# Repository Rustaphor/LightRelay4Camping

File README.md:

LightRelay4Camping ⛺🌳⛰️
==========================

Проект аналогового микромощного фотореле с питанием от PowerBank (USB Type-C) для управления включение-отключение USB-гирлянд
(напряжения питания 5В) в ночное время суток в широким диапазоне регулировки пороговых уровней чувствительности к темноте.
Это простое и надежное DIY устройство целиком аналоговое без прошивок, его несложно повторить начинающему радиолюбителю.
На фото ниже представлен внешний вид собранной электронной платы и устройства в корпусе.

**Фото устройства в корпусе**

## Для чего нужно?
Устройство будет очень полезным в местах кемпинга и отдыха при освещении гирляндами с питанием от PowerBank-ов.
Светодиодные USB-гирлянды, украшающие палатку/автомобиль или другое место размещения на природе с помощью данного устройства
станут автономно-управляемые по уличной освещенности. Самостоятельно включаться в ночное время суток и также отключаться
на рассвете, тем самым экономя заряд PowerBank-а.

[][1]

## Особенности девайса
Фотореле спроектировано просто и надежно. Технически проект представляет несложную реализацию электронной аналоговой
схемотехники (см. _принципиальную схему_) и стандартной цифровой логики (без микроконтроллеров и прошивок), что делает прибор
микро мощным малопотребляемым. А также последнее обстоятельство делает удобным повторение DIY, например в учебной практике.
Для построения электронной схемы выбраны современные широкодоступные электронные компоненты. Ниже кратко представлены
основные достоинства устройства:

- :white_check_mark: Сверхнизкое энергопотребление, значение всего 1мА (в светлое время);
- :white_check_mark: Широкий диапазон регулирования чувствительности срабатывания. От крайне темного, едва видное глазу до рассвета,
когда уже гирлянды не нужны;
- :white_check_mark: Питание 5В от повербанка USB Type-C;
- :white_check_mark: Встроенный супперконденсатор и схема его заряда для решение проблемы самоотключения PowerBank-ов. В ждущем режиме фотореле питается от собственного суперконденсатора.
  Емкости суперконденсатора хватает на 4 часа автономной работы;
- :white_check_mark: Небольшая встроенная временная задержка включения/отключения для минимизации ложных срабатываний часто меняющейся
освещенности, например, под качающимися кронами деревьев;
- 🎁 В качестве бонуса к проектe приложены исходные файлы корпуса для 3D-печати. Корпус имеет следующие особенности:
  - ☔︎ Влагозащищенный
  - 👁 Поворотный глазок с датчиком освещенности (направляется в небо)
  - 🧲 Магнитное крепление 

**Фото устройства со снятой верхней крышкой**

> [!TIP]
> PowerBank-и имеют особенность работы. Они предназначены для питания сравнительно мощных нагрузок. Если ток
> потребления нагрузкой слишком мал (менее 50…100мА), то через небольшой промежуток времени PowerBank переходит в режим
> «сна» (выключается), нагрузка полностью обесточивается.

:blue_book: [Полная техническая документация][1] содержит подробное описание принципа работы, инструкции к изготовлению.

> [!IMPORTANT]
> Подключение устройства к PowerBank-у рекомендуется кабелем *USB: type-C + type-C*. При использовании кабеля *USB: Type-A + Type-C*, автоматическое включение
> PowerBank-а негарантировано (зависит от особенностей конкретного PowerBank-а).

<details>
<summary>:paperclip: Файлы проекта</summary>

## Файлы проекта
Проект состоит из нижеследующих файлов и папок:

**Проектные файлы электронной схемы и печатной платы** в формате [KiCad EDA](https://www.kicad.org/) v8.0, содержат
электронную схему, печатную плату (ПП), правила её трассировки, сопутствующие компоненты (посадочные места, 3D-модели).

```
📄 Camping-LightRelay.kicad_*
📄 lsensor-module.kicad_sch
📄 custom.kicad_sym
📄 fp-lib-table
📄 sym-lib-table
📂 [lib.pretty]
📂 [3dshapes]
```

**Файлы симуляции**
Файлы симуляция [SPICE](https://ru.wikipedia.org/wiki/SPICE_(%D1%81%D0%B8%D0%BC%D1%83%D0%BB%D1%8F%D1%82%D0%BE%D1%80_%D1%8D%D0%BB%D0%B5%D0%BA%D1%82%D1%80%D0%BE%D0%BD%D0%BD%D1%8B%D1%85_%D1%81%D1%85%D0%B5%D0%BC))
отдельных узлов содержатся в отдельной директории

```
📂 [Sims]
```
</details>

[1]: https://github.com/Rustaphor/LightRelay4Camping/wiki "Перейти в раздел Wiki"

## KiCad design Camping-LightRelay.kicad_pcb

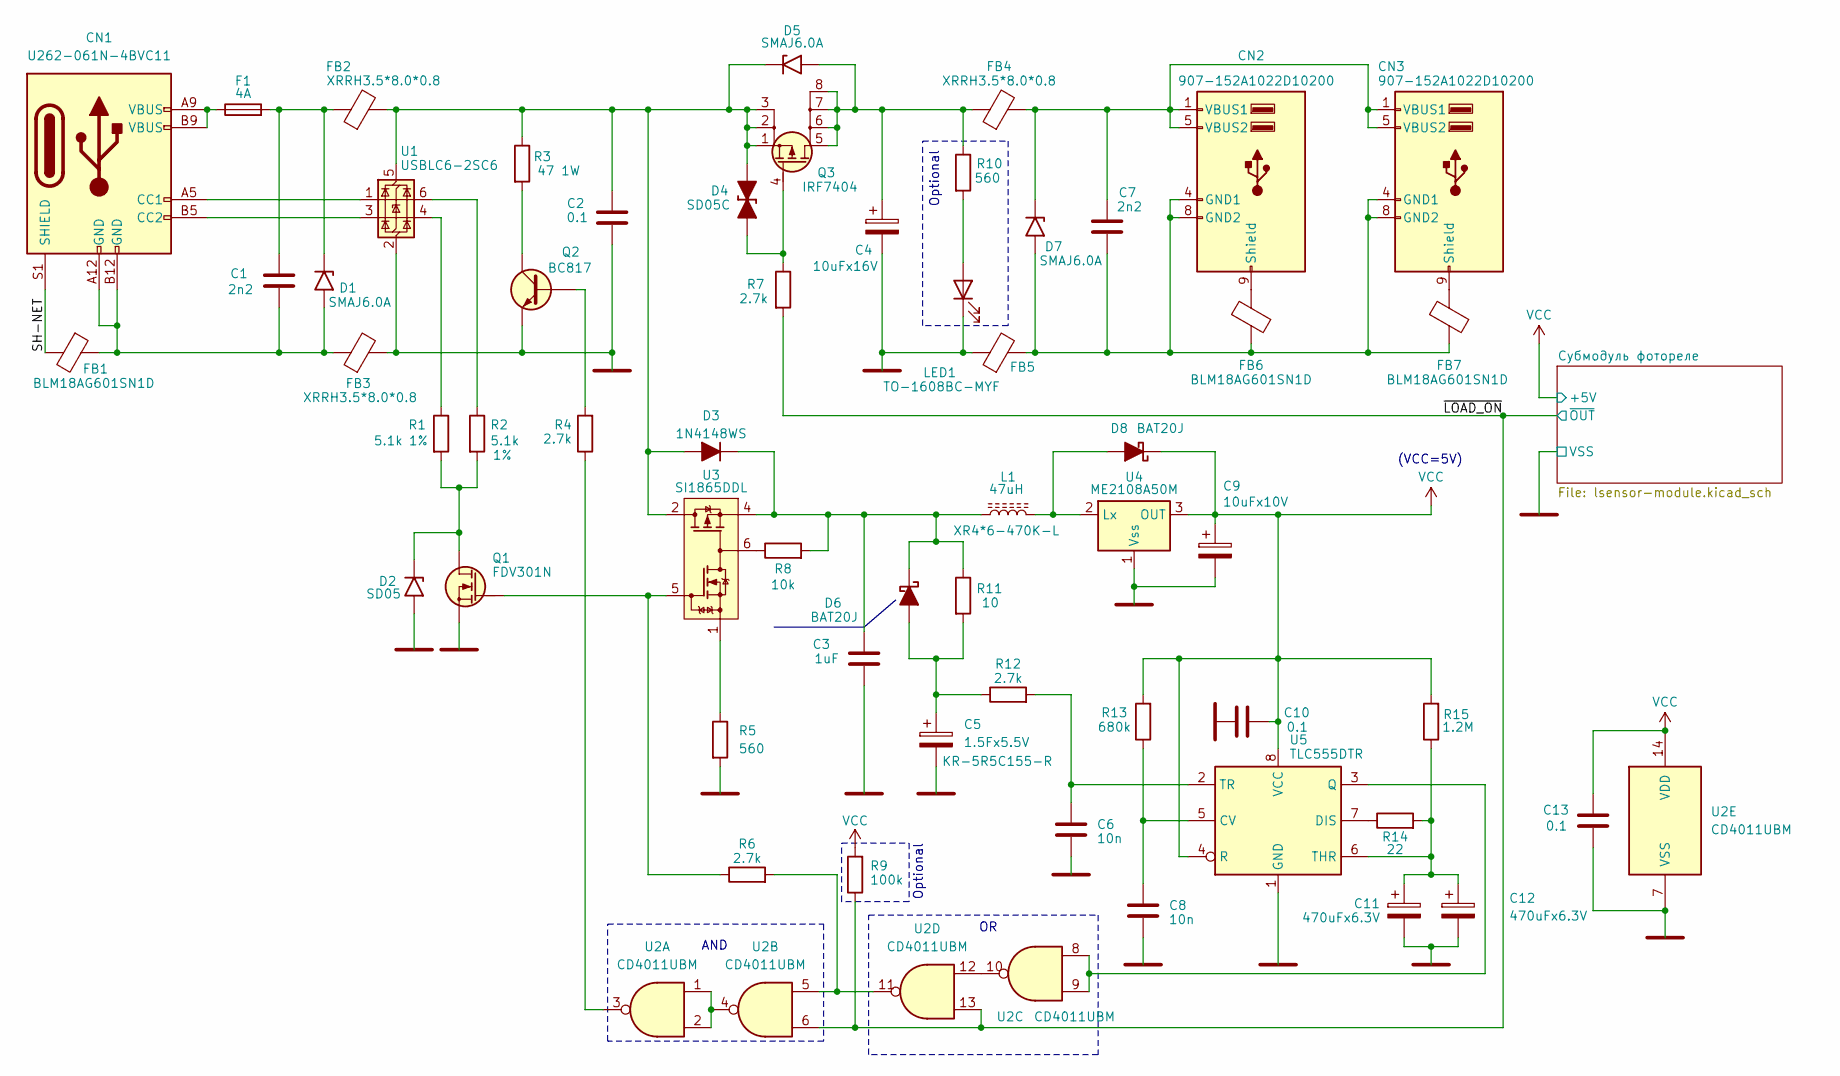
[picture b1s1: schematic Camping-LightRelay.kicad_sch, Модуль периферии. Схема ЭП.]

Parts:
C1, C7: 2n2; C_Disc_D7.5mm_W5.0mm_P7.50mm; Part Number CY2222MD1PEE47J2A8
C2, C10, C13: 0.1; C_0603_1608Metric
C3: 1uF; C_0805_2012Metric
C4: 10uFx16V; CP_EIA-3216-12_Kemet-S_Pad1.58x1.35mm_HandSolder; Part Number CA45-B010K107T
C5: 1.5Fx5.5V; Eaton_KR-5R5C155; Part Number KR-5R5C155-R
C6, C8: 10n; C_0603_1608Metric
C9: 10uFx10V; CP_EIA-3216-12_Kemet-S_Pad1.58x1.35mm_HandSolder; Part Number TC212A106K010Y
C11, C12: 470uFx6.3V; CP_EIA-7343-31_Kemet-D_Pad2.25x2.55mm_HandSolder; Part Number TAJD477K006RNJ
CN1: U262-061N-4BVC11; USB_C_Receptacle_GCT_USB4125-xx-x-0190_6P_TopMnt_Horizontal
CN2, CN3: 907-152A1022D10200; USB_A_DUAL_PORT_Horizontal_Stacked
D1, D5, D7: SMAJ6.0A; D_SMA
D2: SD05; D_SOD-323_HandSoldering
D3: 1N4148WS; D_SOD-323_HandSoldering
D4: SD05C; D_SOD-323_HandSoldering
D6, D8: BAT20J; D_SOD-323_HandSoldering
F1: 4A; Fuse_1206_3216Metric_Pad1.42x1.75mm_HandSolder
FB1, FB6, FB7: BLM18AG601SN1D; L_0603_1608Metric
FB2, FB3, FB4, FB5: XRRH3.5*8.0*0.8; Ferrite_L8.0mm_D3.5mm_P3.81mm_Vertical
L1: 47uH; L_Radial_D6.0mm_P4.00mm; Part Number XR4*6-470K-L
LED1: TO-1608BC-MYF; LED_0603_1608Metric_Pad1.05x0.95mm_HandSolder
Q1: FDV301N; SOT-23
Q2: BC817; SOT-23
Q3: IRF7404; SO-8_3.9x4.9mm_P1.27mm
R1, R2: 5.1k; R_0603_1608Metric_Pad0.98x0.95mm; Tolerance 1%
R3: 47 1W; R_Axial_DIN0309_L9.0mm_D3.2mm_P2.54mm_Vertical
R4, R6, R12: 2.7k; R_0603_1608Metric_Pad0.98x0.95mm
R5: 560; R_0603_1608Metric_Pad0.98x0.95mm
R7: 2.7k; R_0603_1608Metric
R8: 10k; R_0603_1608Metric_Pad0.98x0.95mm
R9: 100k; R_0603_1608Metric_Pad0.98x0.95mm
R10: 560; R_0603_1608Metric
R11: 10; R_0805_2012Metric_Pad1.15x1.40mm
R13: 680k; R_0603_1608Metric_Pad0.98x0.95mm
R14: 22; R_0603_1608Metric_Pad0.98x0.95mm
R15: 1.2M; R_0603_1608Metric_Pad0.98x0.95mm
U1: USBLC6-2SC6; SOT-23-6
U2: CD4011UBM; SOIC-14_3.9x8.7mm_P1.27mm
U3: SI1865DDL; SOT-363_SC-70-6
U4: ME2108A50M; SOT-23-3
U5: TLC555DTR; SOIC-8_3.9x4.9mm_P1.27mm

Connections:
/SH-NET: CN1.S1 (SHIELD), FB1.2
/~LOAD_ON: R7.2, R9.1, U2.6, U2.13; also elsewhere on the board
GNDE: C2.2, C3.2, C4.2, C5.2, C6.2, C8.2, C9.2, C10.1, C11.2, C12.2, C13.2, D2.2 (A2), FB3.2, FB5.1, LED1.1 (K), Q1.2 (S), Q2.2 (E), R5.2, U1.2 (GND), U2.7 (VSS), U4.1 (Vss), U5.1 (GND); also elsewhere on the board
unnamed: CN1.A5 (CC1), U1.1 (I/O1)
unnamed: CN1.B5 (CC2), U1.3 (I/O2)
unnamed: CN1.A9 (VBUS), CN1.B9 (VBUS), F1.1
unnamed: C7.2, CN2.4 (GND1), CN2.8 (GND2), CN3.4 (GND1), CN3.8 (GND2), D7.2 (A2), FB5.2, FB6.1, FB7.1
unnamed: CN2.9 (Shield), FB6.2
unnamed: C7.1, CN2.1 (VBUS1), CN2.5 (VBUS2), CN3.1 (VBUS1), CN3.5 (VBUS2), D7.1 (A1), FB4.2
unnamed: CN3.9 (Shield), FB7.2
unnamed: C1.1, D1.1 (A1), F1.2, FB2.1
unnamed: C1.2, CN1.A12 (GND), CN1.B12 (GND), D1.2 (A2), FB1.1, FB3.1
unnamed: D2.1 (A1), Q1.3 (D), R1.2, R2.2
unnamed: C2.1, D3.2 (A), D4.1 (K), D5.1 (A1), FB2.2, Q3.1 (S), Q3.2 (S), Q3.3 (S), R3.1, U1.5 (VBUS), U3.2 (D2), U3.3 (D2)
unnamed: C3.1, D3.1 (K), D6.1 (K), L1.1, R8.2, R11.1, U3.4 (S2)
unnamed: D4.2 (A), Q3.4 (G), R7.1
unnamed: C4.1, D5.2 (A2), FB4.1, Q3.5 (D), Q3.6 (D), Q3.7 (D), Q3.8 (D), R10.1
unnamed: C5.1, D6.2 (A), R11.2, R12.1
unnamed: D8.2 (A), L1.2, U4.2 (Lx)
unnamed: LED1.2 (A), R10.2
unnamed: Q1.1 (G), R6.1, U3.5 (on/off)
unnamed: Q2.1 (B), R4.2
unnamed: Q2.3 (C), R3.2
unnamed: R1.1, U1.4 (I/O2)
unnamed: R2.1, U1.6 (I/O1)
unnamed: R4.1, U2.3
unnamed: R5.1, U3.1
unnamed: R6.2, U2.5, U2.11
unnamed: R8.1, U3.6
unnamed: U2.1, U2.2, U2.4
unnamed: U2.10, U2.12
unnamed: C8.1, R13.1, U5.5 (CV)
unnamed: R14.1, U5.7 (DIS)
unnamed: U2.8, U2.9, U5.3 (Q)
unnamed: C11.1, C12.1, R14.2, R15.1, U5.6 (THR)
unnamed: C6.1, R12.2, U5.2 (TR)
VCC: C9.1, C10.2, C13.1, D8.1 (K), R9.2, R13.2, R15.2, U2.14 (VDD), U4.3 (OUT), U5.4 (R), U5.8 (VCC); also elsewhere on the board

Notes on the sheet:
Optional
AND
(VCC=5V)

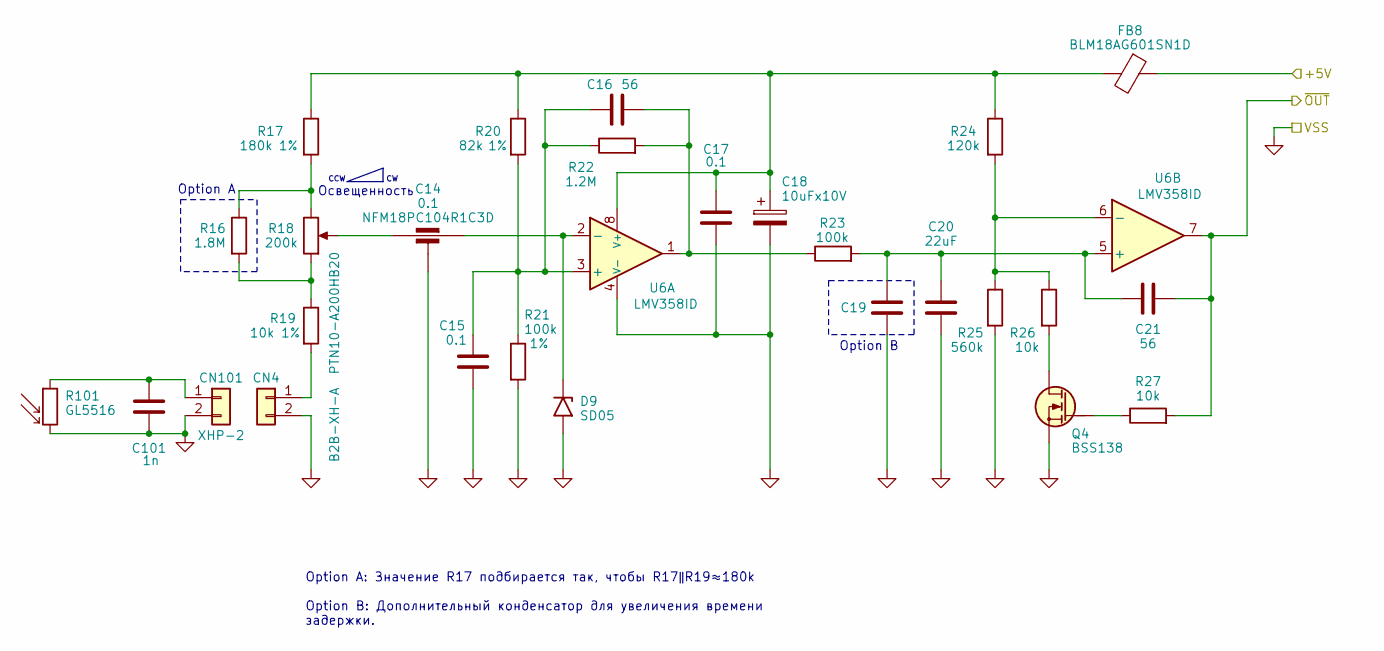
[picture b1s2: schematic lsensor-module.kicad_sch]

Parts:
C14: 0.1; C_0603_3-terminal; Part Number NFM18PC104R1C3D
C15, C17: 0.1; C_0603_1608Metric
C16, C21: 56; C_0603_1608Metric
C18: 10uFx10V; CP_EIA-3216-10_Kemet-I_Pad1.58x1.35mm_HandSolder; Part Number TC212A106K010Y
C19: 10uF; C_0805_2012Metric
C20: 22uF; C_0805_2012Metric
C101: 1n; C_0603_1608Metric
CN4: B2B-XH-A; JST_XH_B2B-XH-AM_1x02_P2.50mm_Vertical
CN101: XHP-2; PinSolder_1x2_P2.54mm
D9: SD05; D_SOD-323_HandSoldering
FB8: BLM18AG601SN1D; L_0603_1608Metric
Q4: BSS138; SOT-23
R16: 1.8M; R_0603_1608Metric
R17: 180k; R_0603_1608Metric; Tolerance 1%
R18: 200k; TRIM_PTN10-A01HB20; Part Number PTN10-A200HB20
R19: 10k; R_0603_1608Metric; Tolerance 1%
R20: 82k; R_0603_1608Metric; Tolerance 1%
R21: 100k; R_0603_1608Metric; Tolerance 1%
R22: 1.2M; R_0603_1608Metric
R23: 100k; R_0603_1608Metric
R24: 120k; R_0603_1608Metric
R25: 560k; R_0603_1608Metric
R26, R27: 10k; R_0603_1608Metric
R101: GL5516; R_LDR_5.1x4.3mm_P3.4mm_Vertical
U6: LMV358ID; SO-8_3.9x4.9mm_P1.27mm

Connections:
/~LOAD_ON: C21.2, R27.2, U6.7; also elsewhere on the board
GND2: C101.2, CN101.2, R101.2
GNDE: C14.2, C15.2, C17.2, C18.2, C19.2, C20.2, CN4.2, D9.2 (A2), Q4.2 (S), R21.2, R25.2, U6.4 (V-); also elsewhere on the board
unnamed: C16.2, R22.2, R23.1, U6.1
unnamed: CN4.1, R19.2
unnamed: C101.1, CN101.1, R101.1
unnamed: C14.3, D9.1 (A1), U6.2 (-)
unnamed: Q4.3 (D), R26.2
unnamed: Q4.1 (G), R27.1
unnamed: R16.2, R18.1 (A), R19.1
unnamed: R16.1, R17.2, R18.3 (E)
unnamed: C14.1, R18.2 (S)
unnamed: C15.1, C16.1, R20.2, R21.1, R22.1, U6.3 (+)
unnamed: C17.1, C18.1, FB8.2, R17.1, R20.1, R24.1, U6.8 (V+)
unnamed: C19.1, C20.1, C21.1, R23.2, U6.5 (+)
unnamed: R24.2, R25.1, R26.1, U6.6 (-)
VCC: FB8.1; also elsewhere on the board

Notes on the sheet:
Option A: Значение R17 подбирается так, чтобы R17ǁR19≈180k Option B: Дополнительный конденсатор для увеличения времени задержки.
Option A
CCW
Освещенность
Option B

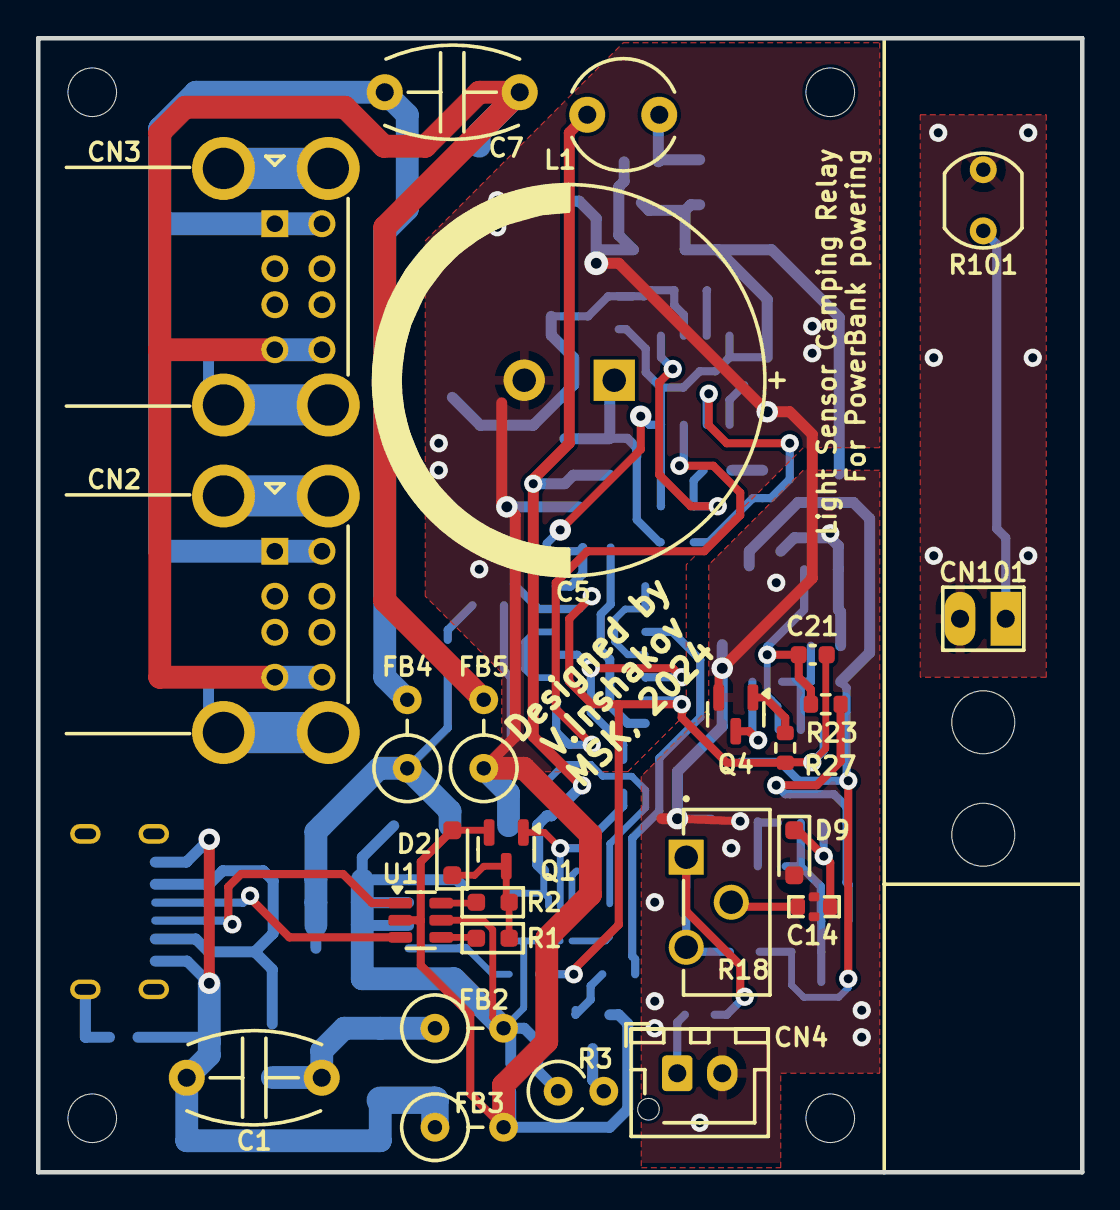
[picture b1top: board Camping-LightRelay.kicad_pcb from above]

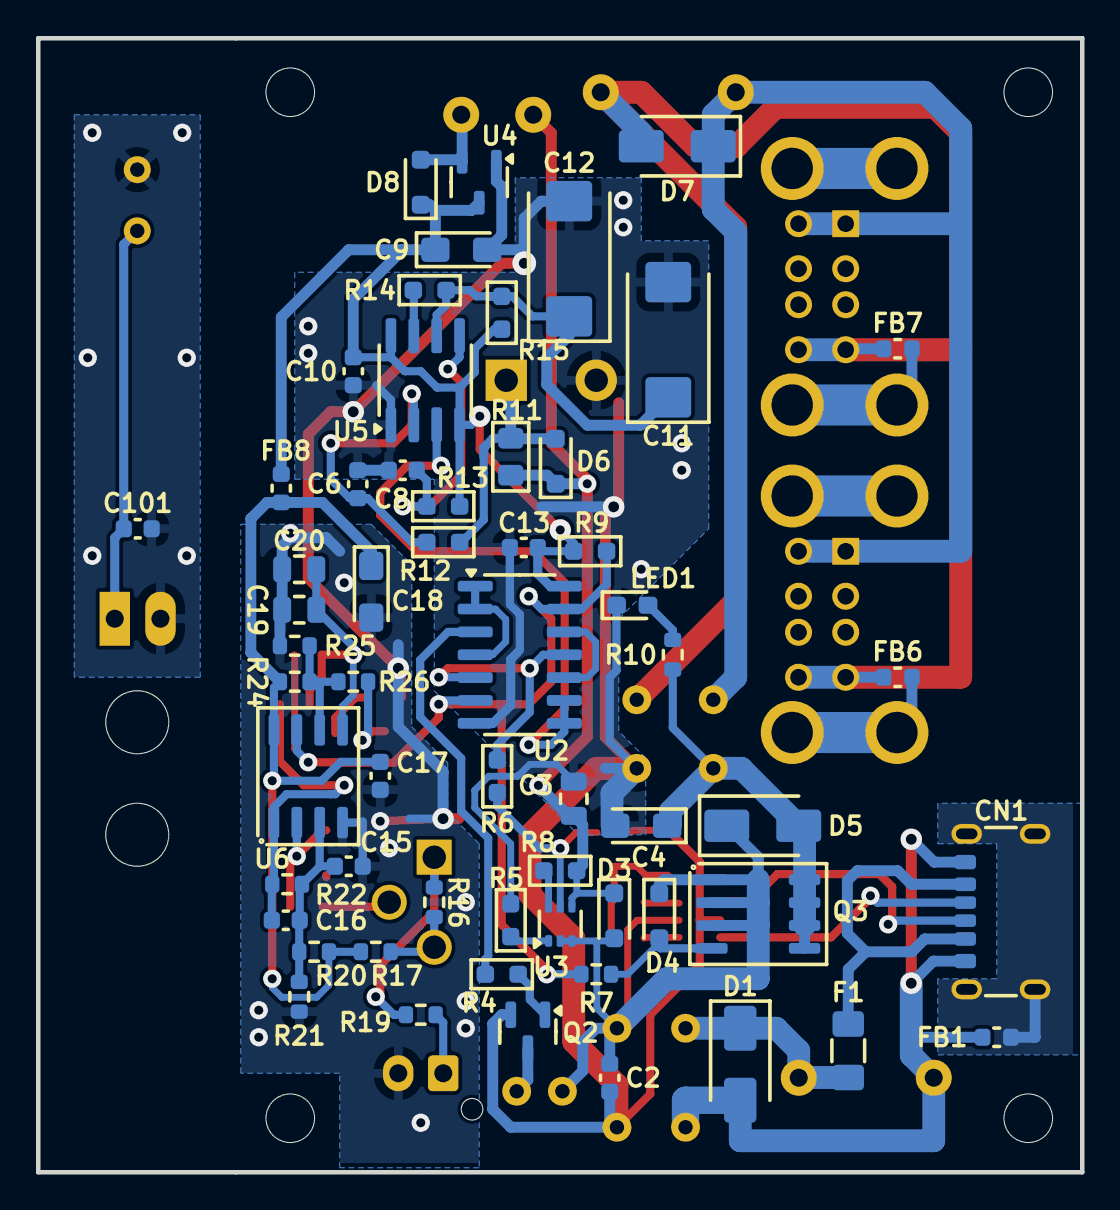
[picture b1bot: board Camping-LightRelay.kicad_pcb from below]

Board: 2 copper layers, 58.0 x 63.0 mm, 91 parts (59 on the bottom side), 51 nets.

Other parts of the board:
HOLE101, HOLE102: MountingHole_3.5mm
MH1, MH1#2, MH1#3, MH3: MountingHole_2.7mm_M2.5

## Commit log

2024-08-17 Правка файла .gitignore
    Добавление ненужных файлов в исключения
2024-08-17 Симуляция электросхемы
    Создание и симуляция SPICE основных блоков фотореле.
2024-08-17 Инвертирование компаратора фотосенсора
    Первоначальная схема сенсора неудобна. Требуется неинвертированный сигнал на выходе; датчик высокоомный и лучше "тянуть" его ближе к "земле".
2024-08-17 Добавление э/схемы и п/платы
    Разработка и схемы и печатной платы с сопутствующими библиотечными компонентами. Схема не собиралась и не тестировалась.
2024-09-24 Добавление э/схемы, SI
    Разработка алгоритма и симуляционной схемы контроллера PowerBank. Проверка работы TLC555 на макетке вживую. Создание символа SI1865
2024-09-30 Отрисовка субмодуля управления питанием
    Принципиальная схема (KiCAD) субмодуля управления PowerBank-ом. Создание электронных компонентов в базе. Выбор и назначение посадочных мест.
2024-10-05 Работа со схемой модуля
    Частичная отрисовка и назначение посадочных мест субмодуля питания от PowerBank. *Работа продолжается*.
2024-10-07 Переделка топологии субмодулей
    Фотореле вынесен в отдельный субмодуль, как дополнительная печатная плата. Схема управления PowerBank-ом перенесена на силовую плату с другими компонентами.
2024-10-07 Назначение посадочных мест схемы
    Дорисовка недостающий э/компонентов и важных 3D-моделей
2024-10-08 Переход на 2-х стороннюю ПП
    Топология ПП выбрана двусторонняя в виду миниатюрности устройства. Изменение посадочных мест под новую топологию.
2024-10-10 Разводка ПП, трассировка, оптимизация
    Отказ от идеи с субмодулем, все разводится на двухсторонней ПП.
    Вынос аналогового фотореле на отдельный лист схемы.
    Разводка двусторонней ПП
2024-10-12 Доделка ПП до финала
    Проверка DRC, подгонка автоправил трассирования дорожек. Корректировка технических ограничений ПП. Расчет номиналов конденсаторов C11, C12.
2024-11-24 Первая сборка production
    Сборка всей конструкции и проверка на ПП, проверка работы
    * Правка посадочного места ионистор C3 и печатной платы для него
    * Замена D3 на обычный 1N4148 из-за утечек Шоттки
    * Замена стабилитрона D4 на двойной TVS-диод, т.к. обнаружился обходной ток от внутреннего DC/DC преобразователя
2024-11-25 Добавление ReaadMe
    Добавление README в корневую директорию
    Удаление файла DNO
2024-12-28 Исправление диаметров отверстий
    Отверстия пропускания кабеля датчика освещенности слишком малы. Увеличено до 3.5мм
2025-02-01 Страница приветствия и симуляция
    Обновляем страницу приветствия и небольшие правки симуляции
2025-06-23 Мелкий рефакторинг
    - Обновление Readme.md
    - Правки в печатную плату
    - Переименование сигналов
    - добавление исключений в .gitignore
2025-06-23 Обновление перед публикацией
    - Удаление лишнего файла симуляции
    - Рефакторинг электрической схемы и печатной платой.
    - Добавление файла симуляции разряда ионистора.
    - Удаление лишних захламляющих файлов
    - Рефакторинг симуляции схем
    - Обновление описания Readme
2025-06-29 Изменение номинала резистора R3
    Возможна нестабильная работа запуска PowerBank-ов при номинале *47 Ом*. Уменьшено до *43* Ом, чтобы ток составлял _100мА_
